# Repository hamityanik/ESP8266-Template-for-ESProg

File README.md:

# ESP8266 (ESP-12E) Programming Schematic & PCB Template for ESProg
ESProg is a programming adapter for ESP8266, ESP8285 and ESP32. It has auto program circuitry like nodemcu, so you don't have to enter bootload mode on target ESP device to upload the program.

This demo template provides library, footprint and sample schematic for KiCad PCB to quick start.
## Target Board Sample Schematic
Minimum required schematic for target board which has ESP module to be programmed like as below.

## ESProg.lib Library Preview

## Footprint Previews

 (@hamityanik)

## Where can I buy one?

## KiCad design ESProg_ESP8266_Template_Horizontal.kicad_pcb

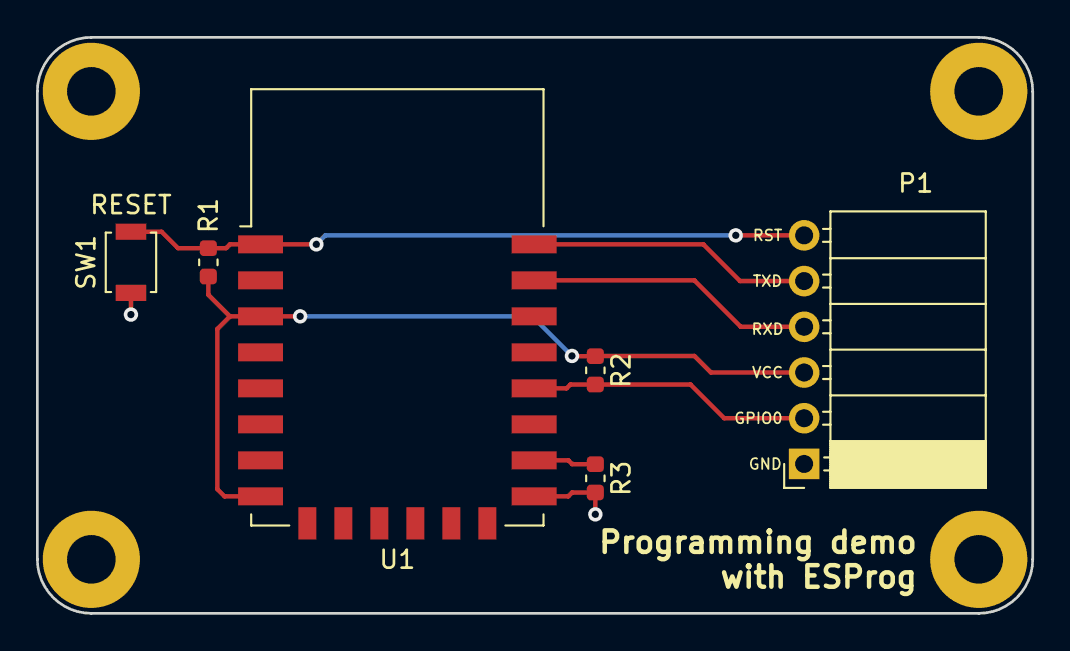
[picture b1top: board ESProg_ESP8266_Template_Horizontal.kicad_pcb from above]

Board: 2 copper layers, 55.3 x 32.0 mm, 10 parts (0 on the bottom side), 7 nets.

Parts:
MH1, MH2, MH3, MH4: M2.5; MountingHole_2.7mm_M2.5_Pad
P1: ESProg Mating Header; ESProg_PinSocket_1x06_P2.54mm_Horizontal
R1: 4.7k; R_0603_1608Metric
R2, R3: 10k; R_0603_1608Metric
SW1: RESET; SW_SPST_B3U-1000P
U1: ESP-12E

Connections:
+3V3: P1.3, R1.1, R2.1, U1.3, U1.8
/GPIO0: P1.2, R2.2, U1.18
/RST: P1.6, R1.2, SW1.2, U1.1
/RXD: P1.4, U1.21
/TXD: P1.5, U1.22
GND: P1.1, R3.2, SW1.1, U1.15
unnamed: R3.1, U1.16

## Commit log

2018-09-01 Some improvements
    Vertical footprint added
2018-09-01 Images added
2018-09-01 Main image added
2018-09-01 README updated
2018-09-01 Sample schematic preview added to README.md
2018-09-01 Updated demo image
2018-09-01 New images added
